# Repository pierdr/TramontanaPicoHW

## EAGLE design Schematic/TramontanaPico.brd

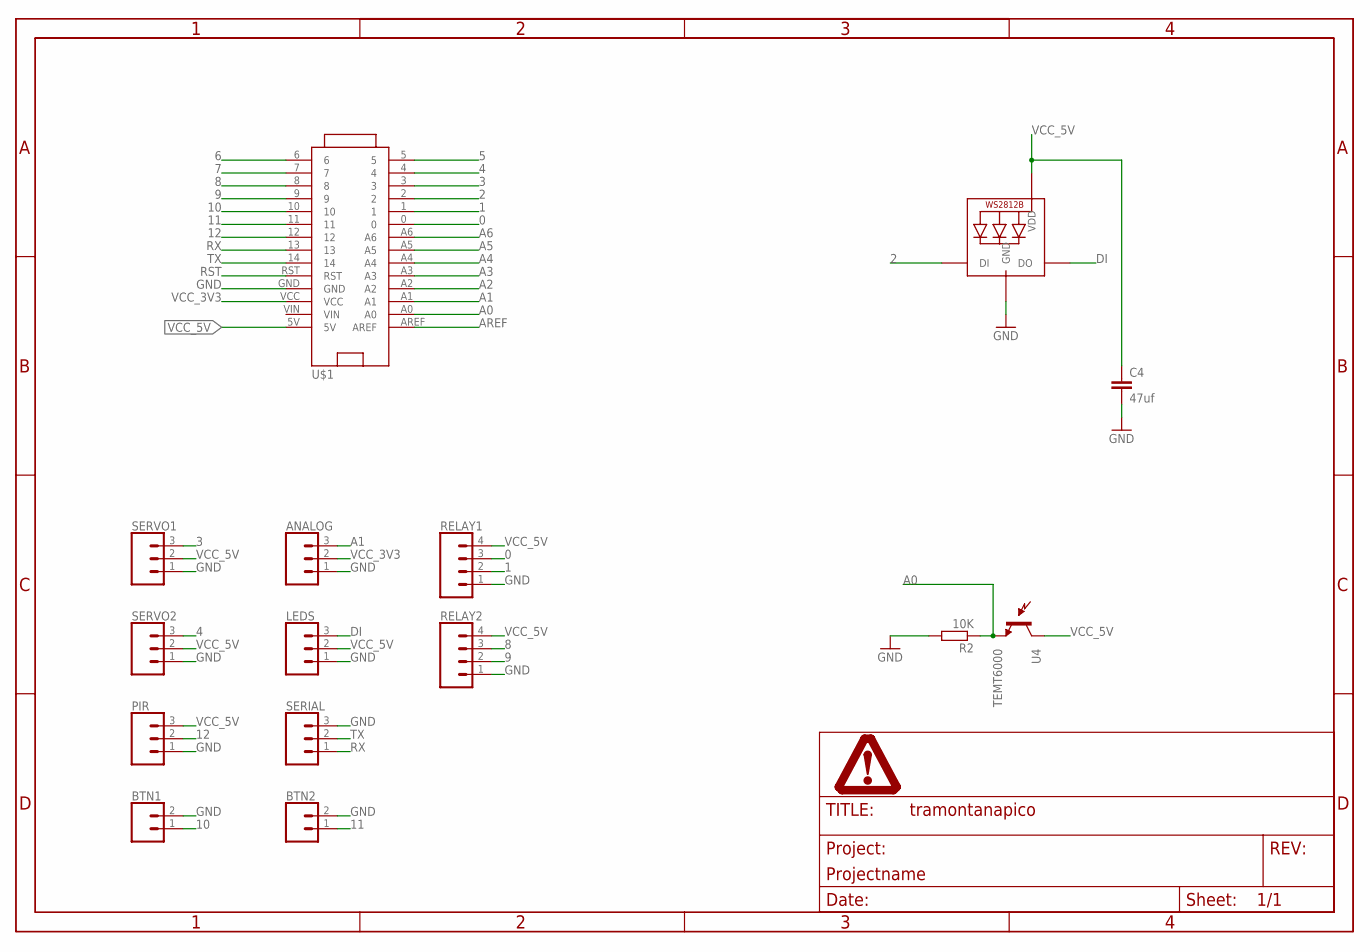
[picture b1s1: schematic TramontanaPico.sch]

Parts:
ANALOG: CONN_03LOCK; 1X03_LOCK
BTN1, BTN2: CONN_02LOCK; 1X02_LOCK
C4: 47uf; C0603
HTTP: FRAME_DINA4_L; DP_LOGO
LED1: WS2812B5050; WS2812B
LEDS: CONN_03LOCK; 1X03_LOCK
PIR: CONN_03LOCK; 1X03_LOCK
R2: 10K; R0603
RELAY1, RELAY2: CONN_04LOCK; 1X04_LOCK
SERIAL: CONN_03LOCK; 1X03_LOCK
SERVO1, SERVO2: CONN_03LOCK; 1X03_LOCK
U4: TEMT6000; TEMT6000-SEN
U$1: MKR1000

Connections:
0: RELAY1.3, U$1.0
1: RELAY1.2, U$1.1
2: LED1.4-DIN (DI), U$1.2
3: SERVO1.3, U$1.3
4: SERVO2.3, U$1.4
5: U$1.5
6: U$1.6
7: U$1.7
8: RELAY2.3, U$1.8
9: RELAY2.2, U$1.9
10: BTN1.1, U$1.10
11: BTN2.1, U$1.11
12: PIR.2, U$1.12
A0: R2.1, U4.EMITTER (E1), U$1.A0
A1: ANALOG.3, U$1.A1
A2: U$1.A2
A3: U$1.A3
A4: U$1.A4
A5: U$1.A5
A6: U$1.A6
AREF: U$1.AREF
DI: LED1.2-DOUT (DO), LEDS.3
GND: ANALOG.1, BTN1.2, BTN2.2, C4.2, LED1.3-GND (GND), LEDS.1, PIR.1, R2.2, RELAY1.1, RELAY2.1, SERIAL.3, SERVO1.1, SERVO2.1, U$1.GND
RST: U$1.RST
RX: SERIAL.1, U$1.13
TX: SERIAL.2, U$1.14
VCC_3V3: ANALOG.2, U$1.VCC
VCC_5V: C4.1, LED1.1-VDD (VDD), LEDS.2, PIR.3, RELAY1.4, RELAY2.4, SERVO1.2, SERVO2.2, U4.COLLECTOR (C1), U$1.5V

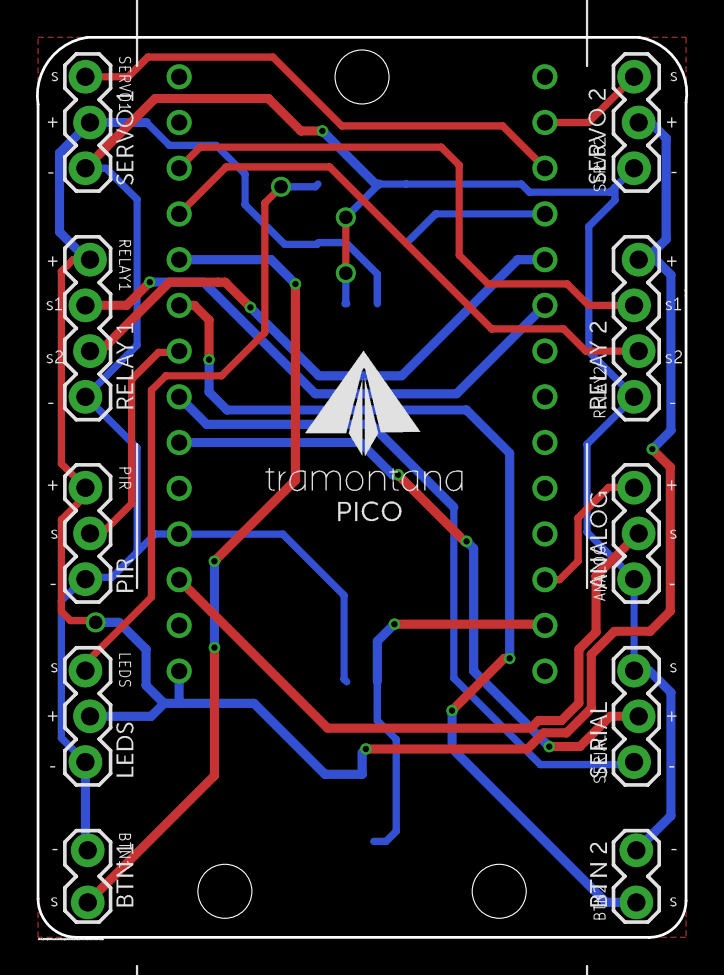
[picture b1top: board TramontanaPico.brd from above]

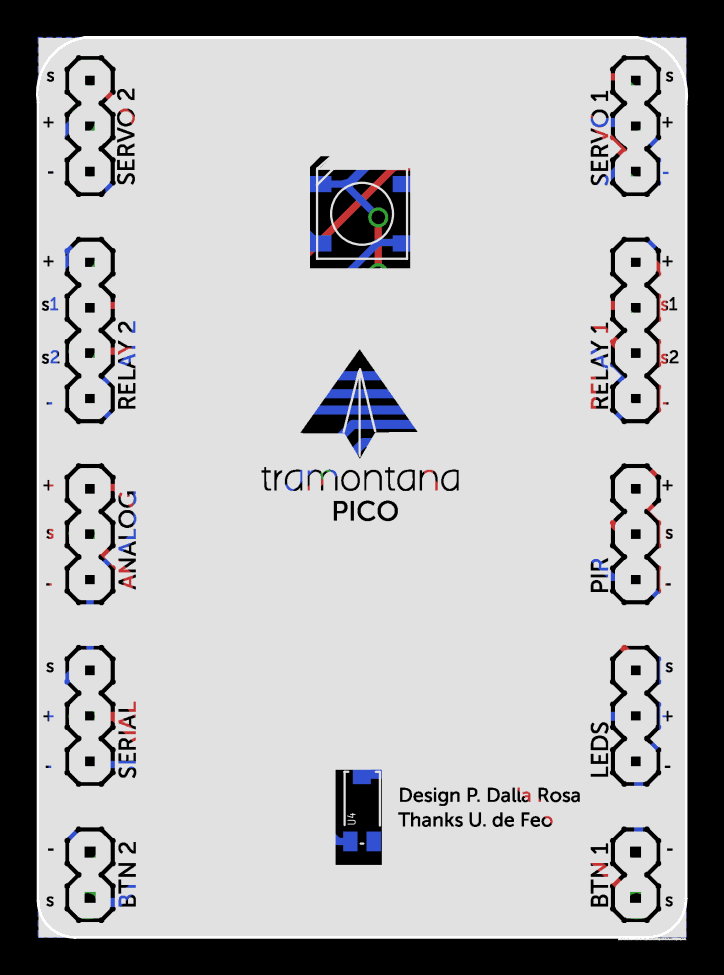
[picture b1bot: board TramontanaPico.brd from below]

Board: 2 copper layers, 36.1 x 50.0 mm, 16 parts (4 on the bottom side), 18 nets.

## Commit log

2018-01-22 Tramontana Pico init
2018-01-28 added button
2018-01-28 improvements
2018-01-28 - small changes to signal naming - routing adjustments (3v3 for analog)
2018-01-28 pier's version
2018-09-14 updated tramontanaPico

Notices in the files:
Schematic/TramontanaPico.brd:
LICENSE: CC-BY-SA
parts and their libraries:
SparkFun-Connectors: Licensing: Creative Commons ShareAlike 4.0 International - https://creativecommons.org/licenses/by-sa/4.0
SparkFun: Licensing: CC v3.0 Share-Alike You are welcome to use this library for commercial purposes.
